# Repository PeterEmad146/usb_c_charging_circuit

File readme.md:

# ⚡ USB-C Power Delivery (PD) Charging Circuit

A compact, high-efficiency USB-C charging circuit designed to negotiate Power Delivery (PD) protocols and safely charge Lithium-ion battery packs. This project aims to replace legacy barrel jacks with a modern, universal USB-C charging interface.

## ✨ Features

* **USB-C Power Delivery (PD) Support:** Negotiates 5V, 9V, 12V, 15V, or 20V depending on the source capabilities and configuration.
* **High-Efficiency Switching:** Uses a synchronous buck/boost topology to minimize heat dissipation.
* **Battery Protection:** Integrated Over-Voltage Protection (OVP), Over-Current Protection (OCP), and Thermal Shutdown.
* **Charge Status Indicators:** Onboard LEDs to indicate 'Charging', 'Fully Charged', and 'Fault' states.
* **Compact Footprint:** Designed to be easily integrated into existing projects or enclosures.

## 📋 Hardware Specifications

| Specification | Value |
| :--- | :--- |
| **Input Connector** | USB-C Receptacle (16-pin or 24-pin) |
| **Input Voltage Range** | 5V - 20V DC (via USB PD) |
| **Max Charge Current** | ~3.0A (Configurable via resistor) |
| **Supported Chemistries**| 1S - 4S Lithium-Ion / LiPo (Configurable) |
| **Charge Controller IC** | *[Insert specific IC here, e.g., IP2368, BQ25792]* |
| **PD Controller IC** | *[Insert specific IC here, e.g., CH224K, FUSB302]* |
| **Operating Temp** | -10°C to 65°C |

## 📐 Schematic & PCB

*(Replace these with actual renders or links to your EDA project files once completed)*

* **Schematic (PDF):** [`docs/schematic.pdf`](#)
* **Gerber Files:** [`hardware/gerbers/`](#)
* **KiCad/Altium Source:** [`hardware/src/`](#)

## 🛒 Key Bill of Materials (BOM)

| Designator | Component | Description |
| :--- | :--- | :--- |
| **U1** | USB PD Sink Controller | Handles CC1/CC2 negotiation |
| **U2** | Charge Controller IC | Regulates current and voltage to the battery |
| **J1** | USB-C Port | SMD USB-C receptacle |
| **L1** | Inductor | High-current power inductor for switching |
| **C1-C4**| MLCC Capacitors | Decoupling and bulk capacitance (X5R/X7R) |

*For the full interactive BOM, please see `docs/ibom.html`.*

## 🚀 Getting Started

### Prerequisites
* A compatible USB-C PD wall adapter and a certified USB-C cable.
* Appropriate battery pack for your configuration.
* Multimeter for initial voltage verification.

### Assembly & Testing
1. **PCB Assembly:** Solder components according to the BOM. Ensure the thermal pad on the Charge Controller IC is properly soldered to the ground plane for heat dissipation.
2. **Initial Test (Without Battery):**
   * Plug in the USB-C cable.
   * Measure the voltage at the battery terminals using a multimeter. It should match the float voltage of your configured battery chemistry (e.g., 4.2V for 1S Li-ion).
   * Verify that the PD negotiation is working (input voltage should match your target PD profile).
3. **Battery Connection:**
   * **⚠️ DANGER:** Ensure polarity is absolutely correct before connecting the battery.
   * Connect the battery and observe the charge status LEDs.
   * Monitor the temperature of the ICs during the first heavy charge cycle.

## ⚠️ Safety Warning

**Lithium batteries are dangerous if handled improperly.**
* This circuit is designed for educational and prototyping purposes.
* Always double-check your resistor configurations for charge current and voltage limits.
* Never charge a damaged or over-discharged battery.
* Do not leave the board unattended during its first charge cycles.
* Use at your own risk. The author is not responsible for property damage or injury.

## 📄 License

This project is licensed under the CERN Open Hardware Licence Version 2 - Strongly Reciprocal (CERN-OHL-S). See the `LICENSE` file for details.

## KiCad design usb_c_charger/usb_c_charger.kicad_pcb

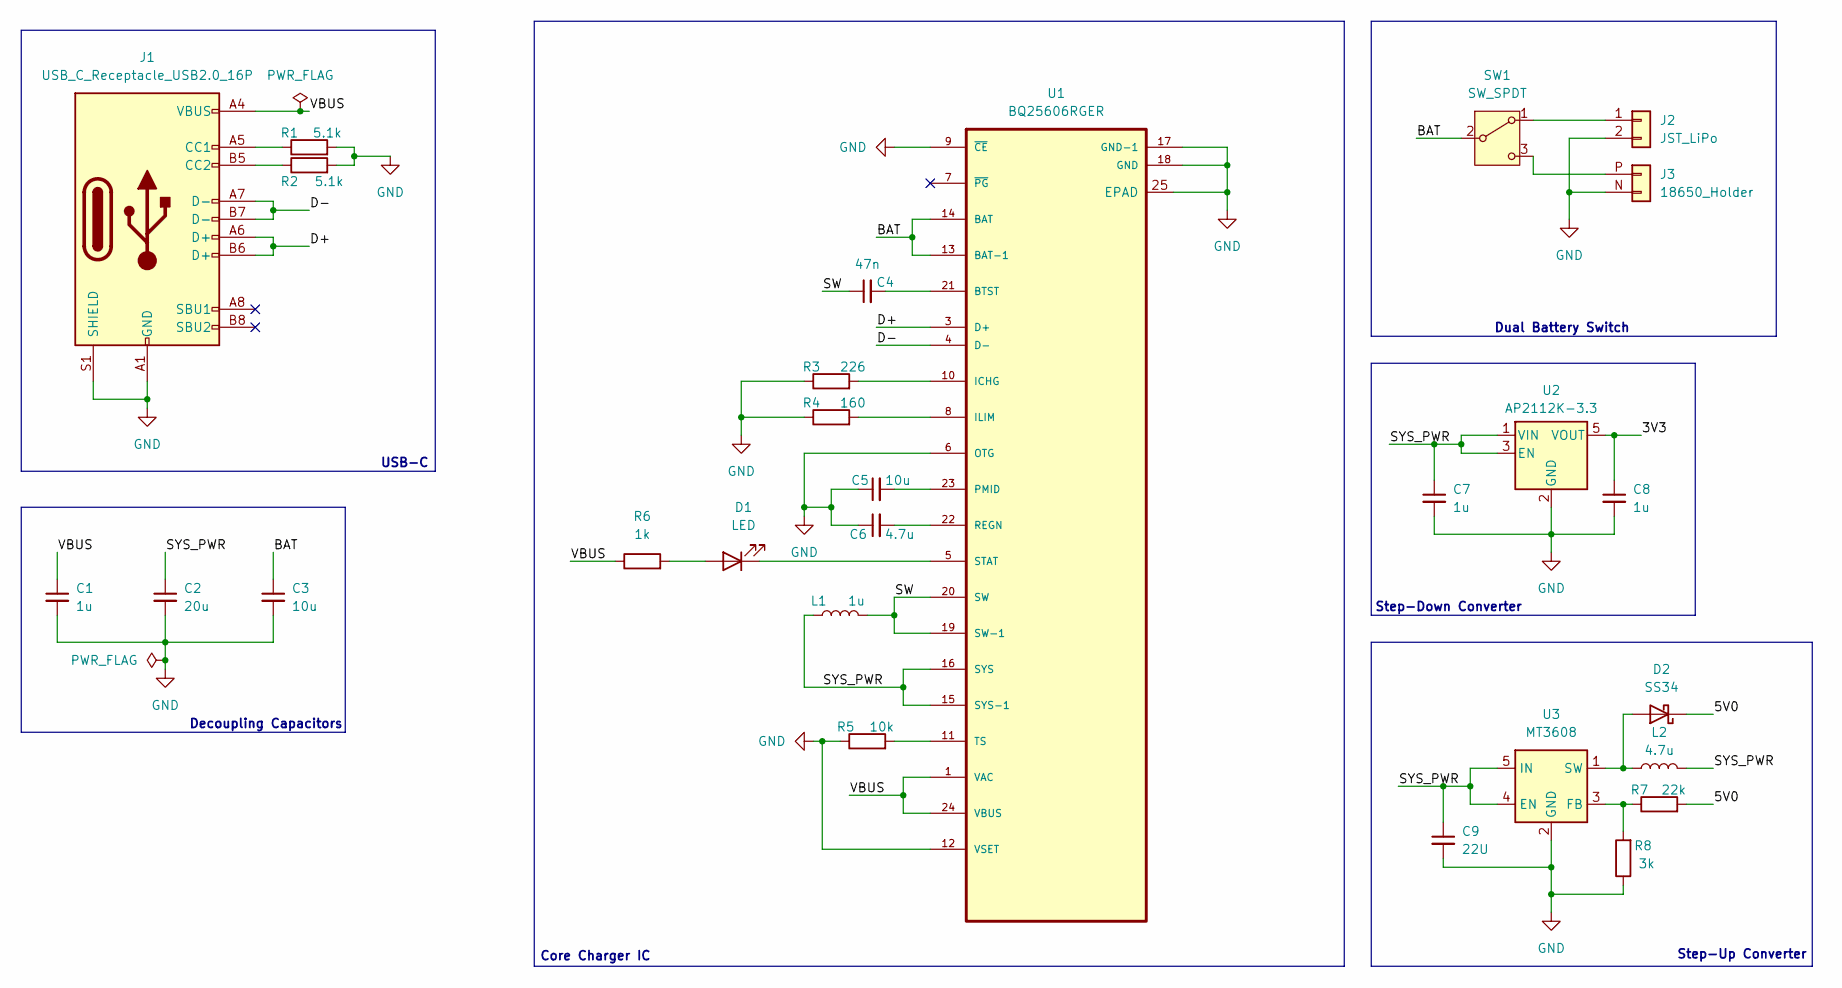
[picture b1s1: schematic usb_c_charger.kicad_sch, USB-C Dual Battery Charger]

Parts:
C1, C7, C8: 1u; C_0805_2012Metric
C2: 20u; C_1206_3216Metric
C3, C5: 10u; C_0805_2012Metric
C4: 47n; C_0805_2012Metric
C6: 4.7u; C_0805_2012Metric
C9: 22U; C_1206_3216Metric
D1: LED; LED_0805_2012Metric
D2: SS34; D_SMA
J1: USB_C_Receptacle_USB2.0_16P; USB_C_Receptacle_HRO_TYPE-C-31-M-12
J2: JST_LiPo; JST_PH_S2B-PH-K_1x02_P2.00mm_Horizontal
J3: 18650_Holder; BAT_1043
L1: 1u; L_6.3x6.3_H3
L2: 4.7u; L_6.3x6.3_H3
R1, R2: 5.1k; R_0805_2012Metric
R3: 226; R_0805_2012Metric
R4: 160; R_0805_2012Metric
R5: 10k; R_0805_2012Metric
R6: 1k; R_0805_2012Metric
R7: 22k; R_0805_2012Metric
R8: 3k; R_0805_2012Metric
SW1: SW_SPDT; SW_EG1218
U1: BQ25606RGER; QFN50P400X400X100-25N
U2: AP2112K-3.3; SOT-23-5
U3: MT3608; SOT-23-6

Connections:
/3V3: C8.1, U2.5 (VOUT)
/5V0: D2.1 (K), R7.2
/BAT: C3.1, SW1.2 (B), U1.13 (BAT-1), U1.14 (BAT)
/D+: J1.A6 (D+), J1.B6 (D+), U1.3 (D+)
/D-: J1.A7 (D-), J1.B7 (D-), U1.4 (D-)
/SW: C4.1, L1.2, U1.19 (SW-1), U1.20 (SW)
/SYS_PWR: C2.1, C7.1, C9.1, L1.1, L2.2, U1.15 (SYS-1), U1.16 (SYS), U2.1 (VIN), U2.3 (EN), U3.4 (EN), U3.5 (IN)
/VBUS: C1.1, J1.A4 (VBUS), J1.A9 (VBUS), J1.B4 (VBUS), J1.B9 (VBUS), R6.1, U1.1 (VAC), U1.24 (VBUS)
GND: C1.2, C2.2, C3.2, C5.1, C6.1, C7.2, C8.2, C9.2, J1.A1 (GND), J1.A12 (GND), J1.B1 (GND), J1.B12 (GND), J1.S1 (SHIELD), J2.2, J3.N (Pin_2), R1.2, R2.2, R3.1, R4.1, R5.1, R8.1, U1.6 (OTG), U1.9 (~CE), U1.12 (VSET), U1.17 (GND-1), U1.18 (GND), U1.25 (EPAD), U2.2 (GND), U3.2 (GND)
unnamed: D1.2 (A), R6.2
unnamed: D1.1 (K), U1.5 (STAT)
unnamed: D2.2 (A), L2.1, U3.1 (SW)
unnamed: J1.A5 (CC1), R1.1
unnamed: J1.B5 (CC2), R2.1
unnamed: J2.1, SW1.1 (A)
unnamed: J3.P (Pin_1), SW1.3 (C)
unnamed: C4.2, U1.21 (BTST)
unnamed: R3.2, U1.10 (ICHG)
unnamed: R4.2, U1.8 (ILIM)
unnamed: C5.2, U1.23 (PMID)
unnamed: C6.2, U1.22 (REGN)
unnamed: R5.2, U1.11 (TS)
unnamed: R7.1, R8.2, U3.3 (FB)

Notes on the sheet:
Step-Down Converter
USB-C
Core Charger IC
Step-Up Converter
Dual Battery Switch
Decoupling Capacitors

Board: 2 copper layers, 28 parts (0 on the bottom side), 23 nets, no tracks yet.

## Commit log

2026-06-02 PCB File Uploaded
2026-06-02 Project File Uploaded
2026-06-02 Schematic File Uploaded
2026-06-02 BQ25606 Component Datasheet Uploaded
2026-06-02 Hardware LICENSE file Uploaded
2026-06-02 First Draft of Readme.md Uploaded
2026-06-02 .gitignore File Added
2026-06-02 BQ25606 IC Part Symbol and Footprint
2026-06-02 Updated Schematic - USB Wiring / dual Battery Connectors / Decoupling Capacitors / Status LED
2026-06-03 Footprints Updated - Added 1043 & EG1218 Footprint
2026-06-03 New PCB Files ignored
2026-06-03 Finished Schematic Routing and PCB Components Initial Placements
